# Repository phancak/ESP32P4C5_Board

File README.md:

# Modular ESP32 Heterogeneous Computing Platform (ESP32-P4 + ESP32-C5)

<div align="center">
  
  <br>
  <em>4-layer PCB diagram.</em>
</div>

## 📑 Quick Access
* [**📂 View Project Schematics (PDF)**](./Schematics/ESP32P4C5_Board.pdf)
* [**📂 View PCB Layout (PDF)**](./PCB_Layout/ESP32P4C5_Board.pdf)

## 📌 Project Overview

A production-grade, high-performance development platform engineered to serve as a modular, reusable core for edge computing, high-bandwidth multimedia processing, and synchronized wireless gateways. 

This repository showcases an advanced asynchronous, dual-MCU topology that isolates intensive computational and real-time interface operations from wireless network stack overhead. By decoupling heavy application logic from communication tasks via a high-speed parallel bus interconnect, the architecture guarantees deterministic processing latency and maximum deployment flexibility across diverse industrial and machine vision domains.

---

## 🏗 System Architecture & Design Philosophy

The system architecture purposefully segregates application compute from wireless networking to maximize throughput and guarantee real-time predictability.

<div align="center">
  
  <br>
  <em>System architecture diagram.</em>
</div>

### 1. Primary Workstation Core: Espressif ESP32-P4
The **ESP32-P4** acts as the primary host, running application firmwares, digital signal processing (DSP), and complex interface state-machines. It interfaces with high-bandwidth peripherals without experiencing interrupt starvation caused by networking radio activity.
*   **Camera FPC Interface:** A dedicated 0.5mm pitch FPC interface supporting parallel/MIPI CSI camera modules. Designed for minimal trace-length skew to support synchronous high-frame-rate image acquisition and local edge execution.
*   **8-Bit Parallel Subsystem:** Exposes a high-speed, parallel digital bus mapped directly onto low-latency GPIO matrices. Engineered to interface directly with legacy parallel hardware, hardware accelerators, rapid external analog-to-digital converters (ADCs), or high-refresh TFT displays.

### 2. Network Co-Processor Subsystem: Espressif ESP32-C5
The **ESP32-C5** operates as a standalone network engine, handling the entirety of the link layer, cryptographic handshakes, and transport layer protocol stacks.
*   **Dual-Band Wi-Fi 6:** Utilizes native 2.4 GHz and 5 GHz radios, providing network resilience against RF congestion, significantly improving communication reliability in dense industrial environments.
*   **Bluetooth 5 (LE):** Managed independently for local out-of-band provisioning, decentralized mesh topologies, and real-time proximity sensing.

### 3. Inter-Processor Communication (IPC): 4-Bit SDIO Bus
Processor synchronization is achieved over a hardware-managed **4-bit SDIO parallel interface**. Unlike highly bottlenecked SPI or serial UART abstractions, this interconnect introduces wide data paths capable of handling high-rate simultaneous dual-band Wi-Fi data routing concurrently with video capture or high-speed I/O manipulation.

---

## 🔌 Hardware Interface Mapping

To fulfill its requirements as a universally integrable module, the layout strictly organizes peripheral pin assignments to mitigate trace crossover and manage signal integrity across high-speed signal groups.

| Peripheral Subsystem | Physical Interface / Interconnect | Target Engineering Application |
| :--- | :--- | :--- |
| **Edge Vision** | 0.5mm Pitch Parallel FPC | CMOS Image Sensors, Edge AI Machine Vision, Asset Monitoring |
| **Parallel Bus** | Low-Impedance GPIO Headers | Legacy Bus Bridging, High-Speed External Converters, Parallel LCDs |
| **Synchronous Serial**| Hardware SPI Bus Headers | High-Frequency IMUs, External Flash Memory, Low-Level Controllers |
| **Asynchronous Serial**| Dedicated Hardware UART | isolated Console Debugging, GNSS Modems, Cellular Modems |
| **Control Bus** | Fast-Mode Plus (Fm+) I2C | Local Telemetry Sensors, Cryptographic Co-Processors, EEPROMs, HMIs |
| **System I/O & Power** | Dual Independent USB-C | Native USB 2.0 Subsystems, Dedicated Programming/Debugging Bridges |

---

## 🚀 Target Production Domain Implementations

*   **Distributed Edge Machine Vision:** Acquires high-fidelity pixel matrices via the FPC interface, executes localized machine learning inference directly on the application core, and marshals real-time vectors safely out through dual-band Wi-Fi 6.
*   **Industrial Automation & Edge HMI:** Interconnects cleanly with external motor controllers, fieldbuses, or dense sensor pods via the 8-bit parallel, SPI, or I2C busses while handling real-time visualization on local touch displays.
*   **Secure IoT Sensor Hubs:** Operates as a security gateway, pulling data from localized wireless sensor clusters via BLE 5 and uploading encrypted data streams to enterprise cloud nodes across secure 5 GHz channels.

---

## 🛠 System Compilation & Initialization Workflow

### Technical Prerequisites
*   **Espressif ESP-IDF SDK v5.3+** (or later stable branches containing target support for the ESP32-P4 architecture).
*   Standard dual-channel USB-to-UART bridging hardware or explicit configuration via internal USB routing layers.

### Compiling and Deployment
To compile and flash the primary application workspace onto the main ESP32-P4 target engine:

```bash
# Navigate to the core processor application repository
cd firmware/main_p4

# Set compilation targets explicitly to the ESP32-P4 hardware register maps
idf.py set-target esp32p4

# Execute target compilation and code optimization pass
idf.py build

# Flash binary payloads onto the hardware module and open serial communication lines
idf.py -p [YOUR_TARGET_PORT] flash monitor
```

## 📝 License & Open Source Compliance
This architecture and firmware codebase are released under the terms of the open-source MIT License. For complete text and details regarding reuse rights, consult the accompanying LICENSE file.

## 🎓 About the Author
I am a recent **Electrical Engineering graduate from the University of British Columbia (UBC)**. This project represents my ability to transition theoretical academic knowledge into a complex, manufacturable high-speed digital system.

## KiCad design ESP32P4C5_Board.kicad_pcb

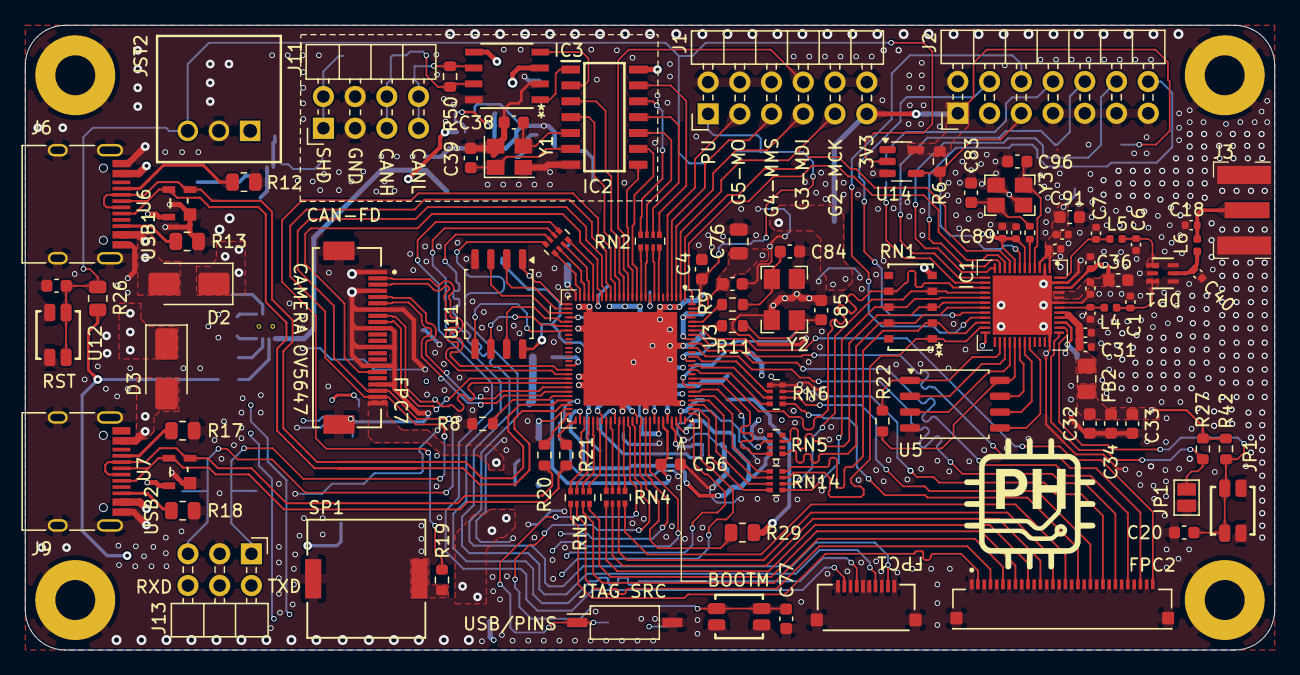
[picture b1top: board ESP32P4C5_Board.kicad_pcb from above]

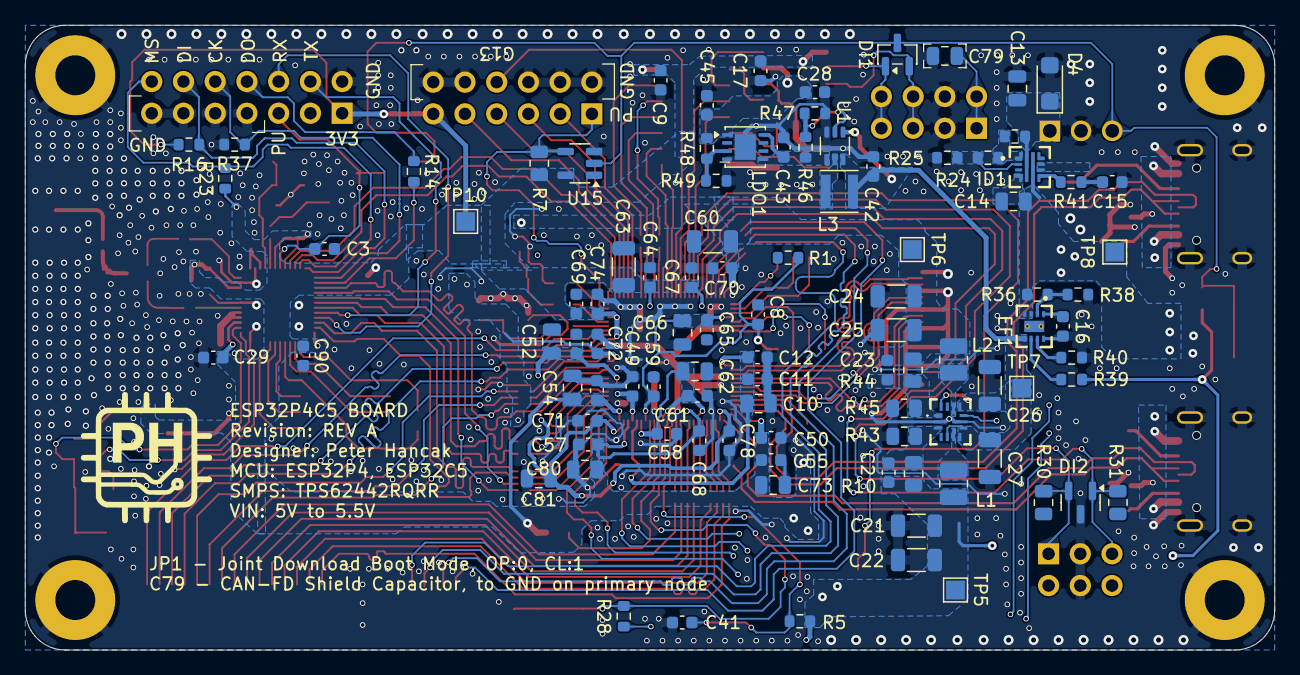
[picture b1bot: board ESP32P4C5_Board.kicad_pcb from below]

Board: 4 copper layers, 100.0 x 50.0 mm, 196 parts (98 on the bottom side), 170 nets.

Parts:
C1: 1p; C_0402_1005Metric
C2, C23, C84, C85: 10p; C_0603_1608Metric
C3, C4, C8, C9, C11, C17, C19, C20, C28, C29, C41, C51, C53, C55, C57, C61, C64, C65, C67, C68, C69, C70, C71, C72, C74, C75, C77, C78: 100n; C_0603_1608Metric
C5: 0p6; C_0402_1005Metric
C6, C30, C31: 0p3; C_0402_1005Metric
C7: 0p4; C_0402_1005Metric
C10, C13, C14, C66: 1u; C_0805_2012Metric
C12, C15, C50: 10n; C_0603_1608Metric
C16: 3n3; C_0603_1608Metric
C18, C40: TBD; C_0402_1005Metric
C21, C22, C24, C25, C60, C63: 10u; C_1206_3216Metric
C26, C27: 4u7; C_1206_3216Metric
C32: 3p_GQM1875C2E3R0BB12D; C_0603_1608Metric
C33, C91: 10u_GRM188Z71A106KA73; C_0603_1608Metric
C34, C36: 100n_GRM188R72A104KA35; C_0603_1608Metric
C35: 10n_GRM1555C1E103JE01; C_0402_1005Metric
C37: 1u_GRM188C71A105MA12; C_0402_1005Metric
C38, C39: 18p; C_0603_1608Metric
C42, C43: 10u; C_0603_1608Metric
C45: 2u2; C_0603_1608Metric
C49, C56, C58, C59, C90: 1u; C_0603_1608Metric
C52, C54, C62, C76, C80, C81: 10u; C_0805_2012Metric
C73: 4u7; C_0805_2012Metric
C79: 10n_500V; C_0805_2012Metric
C83, C96: 8p; C_0603_1608Metric
C89, C94: 1u; C_0402_1005Metric
C92: 1p_GQM1875C2E1R0WB12D; C_0402_1005Metric
C93: 0p6_GQM1875C2ER60BB12; C_0402_1005Metric
D2, D3: SS34-E3/57T; D_SMA
D4: SMF6V0A; D_SMF
DI1: Diode_PESD2CANFD24L-TR; SOT-23
DI2: Diode_PESD5V0U2BT-Q; SOT-23
DP1: DIPLEXER_DPX205950DT-9026A1
EF1: EFUSE_TPS259531DSGR
FB2: BLM21PG601SN1D_0805; C_0805_2012Metric_Pad1.18x1.45mm_HandSolder
FPC1: FPC_10051922-1010ELF; FPC_10051922_1010
FPC2: FPC_AMPHENOL_10051922-3010ELF
FPC7: FPC_FPC05-WFB11-22P111-H20
H1, H2, H3, H4: MountingHole_Pad; MountingHole_3.2mm_M3_Pad
IC1: ESP32-C5HR8; QFN40P600X600X90-49N-D
IC2: XINLUDA XLP2518FDT/ESL; CAN_MCP2518FDT-H_SL
IC3: CAN_ATA6563-GAQW1; CAN_ATA6563_GAQW1
ID1: Ideal_Diode_LM73100RPWR
J1: P4_DEBUG_PINS; PinHeader_2x06_P2.54mm_Horizontal
J2: Debug_Pins; PinHeader_2x07_P2.54mm_Horizontal
J3: SMA PCB END LAUNCH JACK ROUND PO; SMA Clip Mount Adapter (top)
J6, J9: USB_C_Receptacle_USB2.0_16P; USB_C_Receptacle_HRO_TYPE-C-31-M-12
J11: CAN_OUT_HDR; PinHeader_2x04_P2.54mm_Horizontal
J13: I2C1_Headers; PinHeader_2x03_P2.54mm_Horizontal_Court
JP1: SolderJumper_2_Open; SolderJumper-2_P1.3mm_Open_Pad1.0x1.5mm
JST2: JST_S3B-XH-2.54; JST_S3B-XH-SHDRRA3W64P0X250_1X3_990X1150X610P
L1, L2: 470n_muRata DFE252012PD-R47M=P2; L_1008_2520Metric
L3: 4u7_LQH3NPN4R7MMEL; Inductor_LQH3NPN4R7MMEL
L4, L6: 2n4; L_0402_1005Metric
L5: 1n3; L_0402_1005Metric
LDO1: LDO_LDLN050PUR; DFN-8-1EP_3x3mm_P0.65mm_EP1.7x2.05mm
R1, R5, R6, R16, R22, R23, R27, R37, R42: 10k; R_0603_1608Metric
R4: 0R; R_0402_1005Metric
R7, R26, R30, R31: 10k; R_0805_2012Metric
R8: 4k02_1%; R_0603_1608Metric
R9, R11: 0R; R_0603_1608Metric
R10: 88k7; R_0805_2012Metric
R12, R13, R17, R18: 5k1; R_0805_2012Metric
R14, R20, R21: 33R; R_0603_1608Metric
R15: 464k; R_0603_1608Metric
R19: 220R; R_0603_1608Metric
R24: 33k2; R_0603_1608Metric
R25: 110k; R_0603_1608Metric
R28: 10k(1%); R_0603_1608Metric
R29: 10k(1%); R_0805_2012Metric_1
R36, R39, R46: 1M; R_0603_1608Metric
R38: 383k; R_0603_1608Metric
R40: 487R; R_0603_1608Metric
R41: 100R; R_0603_1608Metric
R43: 19k6; R_0805_2012Metric
R44, R45: 68k; R_0805_2012Metric
R47, R49: 100k; R_0603_1608Metric
R48: 316k; R_0603_1608Metric
R50: 120R; R_0603_1608Metric
RN1: RNET_EXB-A10P473J
RN2, RN5, RN6, RN14: 33R; R_Array_Convex_4x0402
RN3, RN4: 10R; R_Array_Convex_4x0402
RN17: 22R; R_Array_Convex_4x0402
SMPS2: SMPS_TPS62442RQRR
SP1: SPKR_CPT-9019A-SMT-TR; SPKR_CPT-9019A
SW1: XUNPU DSHP-01-TS-GER; SW_DIP_SPSTx01_Slide_Copal_CHS-01B_W7.62mm_P1.27mm
TP5, TP6, TP7, TP8, TP10: TestPoint; TestPoint_Pad_1.5x1.5mm
U1: TPS61220DCK; Texas_R-PDSO-G6
U3: ESP32-P4NRW32X; ESP32-P4NRW16
U5: W25Q128JVS; SOIC-8_5.23x5.23mm_P1.27mm
U6, U7: DIODE_TPD2E001DZDR
U9, U12, U13: Button_SKSCLCE010
U11: BY25Q128ESSIG(T); SOP-8_5.28x5.23mm_P1.27mm
U14, U15: SN74LVC1G07DBVR; SOT-23-5
Y1: Crystal_ABM8G-40.000MHZ-18-D2Y-T; Crystal_SMD_Abracon_ABM8G-4Pin_3.2x2.5mm
Y2: ECS-400-10-33B-CKM-TR; Crystal_ECS-400-10-30B-CKM-TR
Y3: ABM8W-48.0000MHZ-7-B1U-T3; Crystal_SMD_Abracon_ABM8AIG-4Pin_3.2x2.5mm

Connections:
3V3+: R30.1, R31.1
5V+: C28.1, C45.2, IC3.3 (VCC), LDO1.1 (OUT), R48.1
/CAN-FD_BUS/CANH: DI1.2 (K2), IC3.7 (CANH), J11.5, J11.6, R50.1
/CAN-FD_BUS/CANL: DI1.1 (K1), IC3.6 (CANL), J11.7, J11.8, R50.2
/CAN-FD_BUS/CLKO/SOF: IC2.3 (CLKO/SOF), U3.15 (GPIO14)
/CAN-FD_BUS/NCS: IC2.13 (NCS), RN2.1 (R1.1)
/CAN-FD_BUS/OSC1: C39.1, IC2.6 (OSC1), Y1.1
/CAN-FD_BUS/OSC2: C38.1, IC2.5 (OSC2), Y1.3
/CAN-FD_BUS/RXCAN: IC2.2 (RXCAN), IC3.4 (RXD)
/CAN-FD_BUS/SCK: IC2.10 (SCK), RN2.3 (R3.1)
/CAN-FD_BUS/SDI: IC2.11 (SDI), RN2.2 (R2.1)
/CAN-FD_BUS/SDO: IC2.12 (SDO), RN2.4 (R4.1)
/CAN-FD_BUS/TXCAN: IC2.1 (TXCAN), IC3.1 (TXD)
/CAN-FD_BUS/~INT1/GPIO1: IC2.8 (~INT1/GPIO1), U3.13 (GPIO12)
/CAN-FD_BUS/~INT: IC2.4 (~INT), U3.16 (GPIO15)
/CAN-FD_BUS/~_INT0/GPIO0/XSTBY: IC2.9 (~_INT0/GPIO0/XSTBY), U3.12 (GPIO11_SPI2_WP)
/ESP32-C5HR8/ANT_2G_M: C5.1, IC1.42 (ANT_2G), L4.2
/ESP32-C5HR8/ANT_5G_M: C7.1, IC1.48 (ANT_5G), L5.2
/ESP32-C5HR8/CHIP_PU: C3.1, IC1.7 (CHIP_PU), J2.5, R6.2, U14.4
/ESP32-C5HR8/GPIO0: IC1.9 (XTAL_32K_P), U3.1 (GPIO1)
/ESP32-C5HR8/GPIO1: IC1.10 (XTAL_32K_N), U3.104 (GPIO0)
/ESP32-C5HR8/GPIO6_SDIO_INT: IC1.15 (GPIO6), RN1.7, U3.87 (GPIO45)
/ESP32-C5HR8/GPIO7_SDIO_DATA1: IC1.16 (GPIO7_SDIO_DATA1), RN1.4, RN14.2 (R2.1)
/ESP32-C5HR8/GPIO8_SDIO_DATA0: IC1.17 (GPIO8_SDIO_DATA0), RN1.8, RN14.1 (R1.1)
/ESP32-C5HR8/GPIO9_SDIO_CLK: IC1.18 (GPIO9_SDIO_CLK), RN1.3, RN5.7 (R2.2)
/ESP32-C5HR8/GPIO10_SDIO_CMD: IC1.19 (GPIO10_SDIO_CMD), RN1.9, RN5.5 (R4.2)
/ESP32-C5HR8/GPIO11_U0TXD: IC1.20 (GPIO11_U0TXD), J2.4
/ESP32-C5HR8/GPIO12_U0RXD: IC1.21 (GPIO12_U0RXD), J2.6
/ESP32-C5HR8/GPIO13_SDIO_DATA3: IC1.22 (GPIO13_SDIO_DATA3), RN1.2, RN14.4 (R4.1)
/ESP32-C5HR8/GPIO14_SDIO_DATA2: IC1.23 (GPIO14_SDIO_DATA2), RN1.1, RN14.3 (R3.1)
/ESP32-C5HR8/GPIO27_BOOT: IC1.37 (GPIO27_BOOT), JP1.2 (B), R27.2
/ESP32-C5HR8/GPIO28_BOOT: C20.2, IC1.38 (GPIO28_BOOT), R42.2, U13.3, U13.4
/ESP32-C5HR8/MTCK: IC1.13 (MTCK), J2.10, R37.1
/ESP32-C5HR8/MTDI: IC1.12 (MTDI), J2.12, R16.2
/ESP32-C5HR8/MTDO: IC1.14 (MTDO), R14.2
/ESP32-C5HR8/MTDO_R: J2.8, R14.1
/ESP32-C5HR8/MTMS: IC1.11 (MTMS), J2.14, R23.2
/ESP32-C5HR8/RST_PWR: C19.2, JST2.3 (RST), R26.2, U12.3, U12.4, U14.2, U15.2
/ESP32-C5HR8/SPICLK: IC1.31 (SPICLK), U5.6 (CLK)
/ESP32-C5HR8/SPICS0: IC1.26 (SPICS0), R22.2, U5.1 (~CS)
/ESP32-C5HR8/SPID: IC1.32 (SPID), U5.5 (DI(IO0))
/ESP32-C5HR8/SPIHD: IC1.30 (SPIHD), U5.7 (IO3)
/ESP32-C5HR8/SPIQ: IC1.27 (SPIQ), U5.2 (DO(IO1))
/ESP32-C5HR8/SPIWP: IC1.28 (SPIWP), U5.3 (IO2)
/ESP32-C5HR8/VDDA1: C30.1, C31.1, FB2.1, IC1.40 (VDDA1), IC1.41 (VDDA2)
/ESP32-C5HR8/VDD_SPI: IC1.29 (VDD_SPI), R22.1, U5.8 (VCC)
/ESP32-C5HR8_RF/ANT: C40.1, DP1.2 (ANT), L6.2
/ESP32-C5HR8_RF/ANT_2G: C1.1, DP1.6 (LO-BAND), L4.1
/ESP32-C5HR8_RF/ANT_5G: C6.1, DP1.4 (HI-BAND), L5.1
/ESP32-C5HR8_RF/ANT_SMA: C18.1, J3.3 (Signal), L6.1
/ESP32-P4NRW16/CHIP_PU: C4.1, J1.1, R7.2, U3.103 (CHIP_PU), U15.4
/ESP32-P4NRW16/CSI_CLKN: FPC7.8, U3.45 (CSI_CLKN)
/ESP32-P4NRW16/CSI_CLKP: FPC7.9, U3.44 (CSI_CLKP)
/ESP32-P4NRW16/CSI_DATAN0: FPC7.2, U3.42 (CSI_DATAN0)
/ESP32-P4NRW16/CSI_DATAN1: FPC7.5, U3.46 (CSI_DATAN1)
/ESP32-P4NRW16/CSI_DATAP0: FPC7.3, U3.43 (CSI_DATAP0)
/ESP32-P4NRW16/CSI_DATAP1: FPC7.6, U3.47 (CSI_DATAP1)
/ESP32-P4NRW16/CSI_REXT: R8.2, U3.48 (CSI_REXT)
/ESP32-P4NRW16/EN_DCDC: SMPS2.10 (EN2), U3.79 (EN_DCDC)
/ESP32-P4NRW16/FB_DCDC: C23.1, R44.2, R45.1, SMPS2.1 (FB2), U3.78 (FB_DCDC)
/ESP32-P4NRW16/FLASH_CK: U3.32 (FLASH_CK), U11.6 (CLK)
/ESP32-P4NRW16/FLASH_CS: R1.2, U3.27 (FLASH_CS), U11.1 (~CS)
/ESP32-P4NRW16/FLASH_D: U3.33 (FLASH_D), U11.5 (DI(IO0))
/ESP32-P4NRW16/FLASH_HOLD: U3.31 (FLASH_HOLD), U11.7 (/HLD/RST(IO3))
/ESP32-P4NRW16/FLASH_Q: U3.28 (FLASH_Q), U11.2 (DO(IO1))
/ESP32-P4NRW16/FLASH_WP: U3.29 (FLASH_WP), U11.3 (/WP(IO2))
/ESP32-P4NRW16/GPIO2_MTCK: J1.9, U3.2 (GPIO2_MTCK)
/ESP32-P4NRW16/GPIO3_MTDI: J1.7, U3.3 (GPIO3_MTDI)
/ESP32-P4NRW16/GPIO4_MTMS: J1.5, U3.4 (GPIO4_MTMS)
/ESP32-P4NRW16/GPIO5_MTDO: J1.3, U3.5 (GPIO5_MTDO)
/ESP32-P4NRW16/GPIO13: J1.8, U3.14 (GPIO13)
/ESP32-P4NRW16/GPIO16: R19.1, U3.17 (GPIO16)
/ESP32-P4NRW16/GPIO17: DI2.2 (K2), FPC7.21, J13.1, R30.2, U3.18 (GPIO17)
/ESP32-P4NRW16/GPIO18: DI2.1 (K1), FPC7.20, J13.5, R31.2, U3.19 (GPIO18)
/ESP32-P4NRW16/GPIO19: FPC7.17, U3.20 (GPIO19)
/ESP32-P4NRW16/GPIO20_SPI_MOSI: RN17.4 (R4.1), U3.22 (GPIO20)
/ESP32-P4NRW16/GPIO21_SPI_MISO: RN17.3 (R3.1), U3.23 (GPIO21)
/ESP32-P4NRW16/GPIO22_SPI_CLK: RN17.2 (R2.1), U3.24 (GPIO22)
/ESP32-P4NRW16/GPIO23_SPI_CS: RN17.1 (R1.1), U3.25 (GPIO23)
/ESP32-P4NRW16/GPIO26_PARLIO: FPC2.2, RN3.1 (R1.1)
/ESP32-P4NRW16/GPIO26_PARLIO_R: RN3.8 (R1.2), U3.55 (GPIO26)
/ESP32-P4NRW16/GPIO27_PARLIO: FPC2.4, RN3.2 (R2.1)
/ESP32-P4NRW16/GPIO27_PARLIO_R: RN3.7 (R2.2), U3.56 (GPIO27)
/ESP32-P4NRW16/GPIO28_PARLIO: FPC2.6, RN3.3 (R3.1)
/ESP32-P4NRW16/GPIO28_PARLIO_R: RN3.6 (R3.2), U3.57 (GPIO28)
/ESP32-P4NRW16/GPIO29_PARLIO: FPC2.8, RN3.4 (R4.1)
/ESP32-P4NRW16/GPIO29_PARLIO_R: RN3.5 (R4.2), U3.58 (GPIO29)
/ESP32-P4NRW16/GPIO30_PARLIO: FPC2.10, RN4.1 (R1.1)
/ESP32-P4NRW16/GPIO30_PARLIO_R: RN4.8 (R1.2), U3.60 (GPIO30)
/ESP32-P4NRW16/GPIO31_PARLIO: FPC2.12, RN4.2 (R2.1)
/ESP32-P4NRW16/GPIO31_PARLIO_R: RN4.7 (R2.2), U3.61 (GPIO31)
/ESP32-P4NRW16/GPIO32_PARLIO: FPC2.14, RN4.3 (R3.1)
/ESP32-P4NRW16/GPIO32_PARLIO_R: RN4.6 (R3.2), U3.63 (GPIO32)
/ESP32-P4NRW16/GPIO33_PARLIO: FPC2.16, RN4.4 (R4.1)
/ESP32-P4NRW16/GPIO33_PARLIO_R: RN4.5 (R4.2), U3.64 (GPIO33)
/ESP32-P4NRW16/GPIO34_BOOTM: C41.2, R5.2, SW1.1, U3.65 (GPIO34_BOOTM)
/ESP32-P4NRW16/GPIO35_BOOTM: C77.2, R28.1, U3.66 (GPIO35_BOOTM), U9.3, U9.4
/ESP32-P4NRW16/GPIO36_BOOTM: R29.1, U3.68 (GPIO36_BOOTM)
/ESP32-P4NRW16/GPIO37_BOOTM_UART0_TXD: J13.2, U3.69 (GPIO37_BOOTM)
/ESP32-P4NRW16/GPIO38_BOOTM_UART0_RXD: J13.6, U3.70 (GPIO38_BOOTM)
/ESP32-P4NRW16/GPIO39_CDATA0_R: RN14.8 (R1.2), U3.80 (GPIO39)
/ESP32-P4NRW16/GPIO40_CDATA1_R: RN14.7 (R2.2), U3.81 (GPIO40)
/ESP32-P4NRW16/GPIO41_CDATA2_R: RN14.6 (R3.2), U3.82 (GPIO41)
/ESP32-P4NRW16/GPIO42_CDATA3_R: RN14.5 (R4.2), U3.83 (GPIO42)
/ESP32-P4NRW16/GPIO43_CCLK_R: RN5.2 (R2.1), U3.84 (GPIO43)
/ESP32-P4NRW16/GPIO44_CCMD_R: RN5.4 (R4.1), U3.86 (GPIO44)
/ESP32-P4NRW16/GPIO47_PARLIO: FPC2.18, RN6.1 (R1.1)
/ESP32-P4NRW16/GPIO47_PARLIO_R: RN6.8 (R1.2), U3.89 (GPIO47)
/ESP32-P4NRW16/GPIO48_PARLIO: FPC2.20, RN6.2 (R2.1)
/ESP32-P4NRW16/GPIO48_PARLIO_R: RN6.7 (R2.2), U3.90 (GPIO48)
/ESP32-P4NRW16/GPIO49_PARLIO: FPC2.22, RN6.3 (R3.1)
/ESP32-P4NRW16/GPIO49_PARLIO_R: RN6.6 (R3.2), U3.92 (GPIO49)
/ESP32-P4NRW16/GPIO51: FPC2.24, U3.94 (GPIO51)
/ESP32-P4NRW16/GPIO52: FPC2.26, U3.95 (GPIO52)
/ESP32-P4NRW16/GPIO53: FPC2.28, U3.97 (GPIO53)
/ESP32-P4NRW16/GPIO54: FPC2.30, U3.98 (GPIO54)
/ESP32-P4NRW16/P4_USB_HS_DN: J6.A7 (D-), J6.B7 (D-), U3.49 (DM), U6.2 (IO1)
/ESP32-P4NRW16/P4_USB_HS_DP: J6.A6 (D+), J6.B6 (D+), U3.50 (DP), U6.3 (IO2)
/ESP32-P4NRW16/SP+: R19.2, SP1.1
/ESP32-P4NRW16/SPI2_CK: RN2.6 (R3.2), U3.10 (GPIO9_SPI2_CK)
/ESP32-P4NRW16/SPI2_CS: RN2.8 (R1.2), U3.7 (GPIO7_SPI2_CS)
/ESP32-P4NRW16/SPI2_MISO: RN2.5 (R4.2), U3.11 (GPIO10_SPI2_MISO)
/ESP32-P4NRW16/SPI2_MOSI: RN2.7 (R2.2), U3.8 (GPIO8_SPI2_MOSI)
/ESP32-P4NRW16/USB1P1_N: J9.A7 (D-), J9.B7 (D-), R20.1, U7.2 (IO1)
/ESP32-P4NRW16/USB1P1_P: J9.A6 (D+), J9.B6 (D+), R21.1, U7.3 (IO2)
/ESP32-P4NRW16/USB1P1_R_N: R20.2, U3.52 (GPIO24_USB1P1_N0)
/ESP32-P4NRW16/USB1P1_R_P: R21.2, U3.53 (GPIO25_USB1P1_P0)
/ESP32-P4NRW16/XTAL_N: R11.1, U3.99 (XTAL_N)
/ESP32-P4NRW16/XTAL_P: R9.1, U3.100 (XTAL_P)
/Interfaces/SPI_CLK: FPC1.7, RN17.7 (R2.2)
/Interfaces/SPI_CS: FPC1.9, RN17.8 (R1.2)
/Interfaces/SPI_MISO: FPC1.4, RN17.6 (R3.2)
/Interfaces/SPI_MOSI: FPC1.2, RN17.5 (R4.2)
/Power_Management/DVDT_0: C15.2, R41.2
/Power_Management/DVDT_1: C16.2, EF1.1 (DVDT)
/Power_Management/DVDT_R: ID1.7 (DVDT), R41.1
/Power_Management/EN/UVLO_0: ID1.1 (EN/UVLO), R15.2, R24.1
/Power_Management/EN/UVLO_1: EF1.2 (EN/UVLO), R36.2, R38.1
/Power_Management/FB1: C2.1, R10.2, R43.1, SMPS2.3 (FB1)
/Power_Management/ILM: EF1.7 (ILM), R40.1
/Power_Management/OVLO: ID1.2 (OVLO), R24.2, R25.1
/Power_Management/PWR+: C13.2, D4.1 (A1), ID1.5 (IN), JST2.1 (PWR+), R15.1
/Power_Management/PWR_C+: C14.2, D2.1 (K), D3.1 (K), EF1.3 (IN), EF1.4 (IN__1), ID1.6 (OUT), R36.1, TP8.1 (1_1)
/Power_Management/SW1: L1.1, SMPS2.6 (SW1)
/Power_Management/SW2: L2.1, SMPS2.12 (SW2)
/Power_Management/~FLT: EF1.6 (~FLT), R39.2
ESP_3V3: C2.2, C9.1, C17.1, C21.2, C22.2, C29.1, C32.1, C33.1, C34.1, C35.1, C36.2, C37.1, C50.1, C53.1, C54.1, C55.1, C57.1, C63.1, C64.1, C67.1, C68.1, C69.1, C73.1, C74.1, C75.1, C76.1, C80.1, C89.1, C90.1, C91.1, C92.1, C93.1, C94.1, FB2.2, FPC7.22, IC1.1 (VDDA6), IC1.3 (VDDA7), IC1.6 (VDDA8), IC1.8 (VDDPST1), IC1.24 (VDDPST2), IC1.39 (VDDPST3), IC1.44 (VDDA3), IC1.45 (VDDA4), IC1.46 (VDDA5), IC2.14 (VDD), IC3.5 (VIO), J1.11, J2.1, L1.2, R5.1, R6.1, R7.1, R10.1, R16.1, R23.1, R26.1, R27.1, R28.2, R29.2, R39.1, R42.1, RN1.5, TP5.1 (1_1), TP10.1 (1_1), U3.9 (VDD_LP), U3.21 (VDD_IO_0), U3.51 (VDD_USBPHY), U3.62 (VDD_IO_4), U3.75 (VDD_LDO), U3.77 (VDD_DCDCC), U3.96 (VDD_IO_6), U3.101 (VDDANA), U3.102 (VBAT), U14.5 (VCC), U15.5 (VCC)
ESP_FLASH: C8.1, C59.1, C65.1, C66.1, R1.1, U3.30 (VDD_FLASHIO), U3.71 (VDDO_FLASH), U11.8 (VCC)
ESP_LDO_VDDO_3: C10.1, C11.1, C12.1, C56.1, U3.41 (VDD_MIPI_DPHY), U3.73 (VDDO_3)
ESP_LDO_VDDO_4: C49.1, C51.1, C52.1, U3.74 (VDDO_4), U3.85 (VDD_IO_5)
ESP_LDO_VDDO_PSRAM: C58.1, C61.1, C62.1, U3.59 (VDD_PSRAM_0), U3.67 (VDD_PSRAM_1), U3.72 (VDDO_PSRAM)
ESP_VDD_HP: C23.2, C24.2, C25.2, C60.1, C70.1, C71.1, C72.1, C78.1, C81.1, L2.2, R44.1, TP6.1 (1_1), U3.26 (VDD_HP_0), U3.54 (VDD_HP_1), U3.76 (VDD_HP_2), U3.91 (VDD_HP_3)
GND: C1.2, C3.2, C4.2, C5.2, C6.2, C7.2, C8.2, C9.2, C10.2, C11.2, C12.2, C13.1, C14.1, C15.1, C16.1, C17.2, C18.2, C19.1, C20.1, C21.1, C22.1, C24.1, C25.1, C26.1, C27.1, C28.2, C29.2, C30.2, C31.2, C32.2, C33.2, C34.2, C35.2, C36.1, C37.2, C38.2, C39.2, C40.2, C41.1, C42.1, C43.1, C45.1, C49.2, C50.2, C51.2, C52.2, C53.2, C54.2, C55.2, C56.2, C57.2, C58.2, C59.2, C60.2, C61.2, C62.2, C63.2, C64.2, C65.2, C66.2, C67.2, C68.2, C69.2, C70.2, C71.2, C72.2, C73.2, C74.2, C75.2, C76.2, C77.1, C78.2, C79.1, C80.2, C81.2, C83.2, C84.2, C85.2, C89.2, C90.2, C91.2, C92.2, C93.2, C94.2, C96.2, D4.2 (A2), DI1.3 (CC), DI2.3 (CC), DP1.1 (GND), DP1.3 (GND), DP1.5 (GND), EF1.8 (GND), EF1.9 (GND__1), FPC1.1, FPC1.3, FPC1.5, FPC1.6, FPC1.8, FPC1.10, FPC1.11 (MP1), FPC1.12 (MP2), FPC2.1, FPC2.3, FPC2.5, FPC2.7, FPC2.9, FPC2.11, FPC2.13, FPC2.15, FPC2.17, FPC2.19, FPC2.21, FPC2.23, FPC2.25, FPC2.27, FPC2.29, FPC2.SH1, FPC2.SH2, FPC7.1, FPC7.4, FPC7.7, FPC7.10, FPC7.13, FPC7.16, FPC7.19, FPC7.23, FPC7.24, H1.1 (1_1), H2.1 (1_1), H3.1 (1_1), H4.1 (1_1), IC1.2 (GND_1), IC1.36 (GPIO26_BOOT), IC1.43 (GND_2), IC1.47 (GND_3), IC1.49 (GND_4), IC2.7 (VSS), IC3.2 (GND), IC3.8 (STBY), ID1.4 (PGTH), ID1.8 (GND), ID1.9 (IMON), J1.2, J1.4, J1.6, J1.10, J1.12, J2.2, J2.3, J2.7, J2.9, J2.11, J2.13, J3.1 (GND), J3.2 (GND), J6.A1 (GND), J6.A12 (GND), J6.B1 (GND), J6.B12 (GND), J6.S1 (SHIELD), J9.A1 (GND), J9.A12 (GND), J9.B1 (GND), J9.B12 (GND), J9.S1 (SHIELD), J11.3, J11.4, J13.3, J13.4, JP1.1 (A), JST2.2 (PWR-), LDO1.4 (GND_1), LDO1.9 (GND_2), R8.1, R12.2, R13.2, R17.2, R18.2, R25.2, R37.2, R38.2, R40.2, R43.2, R45.2, R47.2, R49.2, RN6.4 (R4.1), RN6.5 (R4.2), SMPS2.2 (GND_1), SMPS2.9 (GND_2), SP1.2, SW1.2, U1.3 (GND), U3.105 (GND), U5.4 (GND), U6.1 (GND), U7.1 (GND), U9.1, U9.2, U11.4 (GND), U12.1, U12.2, U13.1, U13.2, U14.3 (GND), U15.3 (GND), Y1.2, Y1.4, Y2.2, Y2.4, Y3.2, Y3.4
unnamed: C83.1, R4.2, Y3.1
unnamed: C84.1, R9.2, Y2.1
unnamed: C85.1, R11.2, Y2.3
unnamed: C96.1, IC1.4 (XTAL_N), Y3.3
unnamed: IC1.5 (XTAL_P), R4.1
unnamed: J6.A5 (CC1), R12.1
unnamed: J6.B5 (CC2), R13.1
unnamed: J9.A5 (CC1), R17.1
unnamed: J9.B5 (CC2), R18.1
unnamed: C79.2, J11.1, J11.2
unnamed: C43.2, LDO1.5 (EN), LDO1.8 (IN), R46.1, U1.4 (VOUT)
unnamed: LDO1.3 (FB), R48.2, R49.1
unnamed: R46.2, R47.1, U1.2 (FB)
unnamed: L3.2, U1.5 (L)
PWR_D+: C26.2, C27.2, C42.2, EF1.5 (OUT), L3.1, SMPS2.5 (MODE_/SYNC), SMPS2.7 (VIN1), SMPS2.8 (EN1), SMPS2.11 (VIN2), SMPS2.14 (COMP_/FSET), TP7.1 (1_1), U1.1 (VIN), U1.6 (EN)
VBUS1+: D2.2 (A), J6.A4 (VBUS), J6.A9 (VBUS), J6.B4 (VBUS), J6.B9 (VBUS), U6.4 (VCC)
VBUS2+: D3.2 (A), J9.A4 (VBUS), J9.A9 (VBUS), J9.B4 (VBUS), J9.B9 (VBUS), U7.4 (VCC)

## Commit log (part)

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2026-05-09 Updated notes
2026-05-13 SMA Update
2026-05-24 QSPI Memory Bus
2026-06-03 Interface Update
2026-06-11 Small trace layout fixes
2026-06-16 Power rail update
2026-06-19 5V SMPS
